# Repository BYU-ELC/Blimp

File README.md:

# Air Blimp
Sources, code, and files for the Air Blimp project

This code is implemented as a Bluetooth app. 
A helium balloon will keep the blimp suspended in air. This Bluetooth app will have access to the vector thrusters on either side, and when signified, these will steer the blimp in the desired direction.

This main  folder includes:
<br>The PCB Schematic File:     Blimp PCB v27.sch
<br>The PCB Board File:         Blimp_PCB_v50.brd
<br>The Laser cut vector file:  blimp_cut_v3.dxf
<br>The Arduino Code:           blimp.ino

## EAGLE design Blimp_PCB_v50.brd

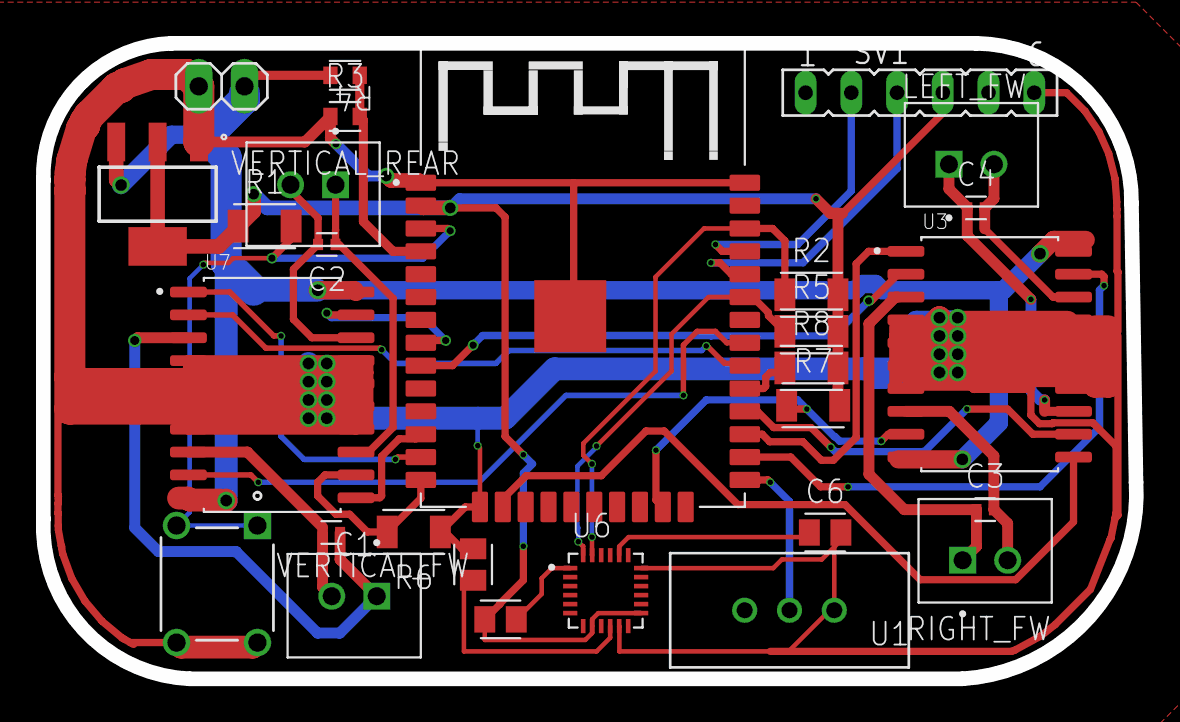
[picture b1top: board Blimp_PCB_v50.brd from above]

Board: 2 copper layers, 60.7 x 35.3 mm, 28 parts (0 on the bottom side), 34 nets.

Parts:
BATTERY_CONN: PINHD-1X2; 1X02
C1, C2, C3, C4: 330p; CAPC1005X60
C5: .1uF; CAPC2012X110
C6: 2200pF; CAPC2012X110
C7: .01uF; CAPC2012X110
LEFT_FW: B2B-XH-A(LF)(SN); JST_B2B-XH-A(LF)(SN)
R1, R6, R7, R8: RESC3216X70
R2, R5: 4.7k; RESC3216X70
R3, R4: RESC1608X60
RESETBUTTON: 1-1825910-0; SWITCH_1-1825910-0
RIGHT_FW: B2B-XH-A(LF)(SN); JST_B2B-XH-A(LF)(SN)
SV1: FE06
U1: 1825159-1; SW3-SLIDE-2POL_P98
U3, U7: L293DD; SOIC127P1032X265-20N
U4: LD1117S33TR; SOT230P700X180-4N
U5: ESP-WROOM-32; MODULE_ESP-WROOM-32
U6: MPU-6050; QFN50P400X400X95-24N
VERTICAL_FW: B2B-XH-A(LF)(SN); JST_B2B-XH-A(LF)(SN)
VERTICAL_REAR: B2B-XH-A(LF)(SN); JST_B2B-XH-A(LF)(SN)

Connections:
GND: BATTERY_CONN.2, C5.1, C6.2, R3.1, R6.1, RESETBUTTON.3, RESETBUTTON.4, SV1.6, U1.3, U3.4, U3.5, U3.6, U3.7, U3.14, U3.15, U3.16, U3.17, U4.1, U5.1, U5.1.1, U5.15, U5.38, U6.11, U6.18, U7.4, U7.5, U7.6, U7.7, U7.14, U7.15, U7.16, U7.17
IO0: U1.2, U5.25
IO4: U3.19, U5.26
IO5: R8.1, U5.29
IO12: R6.2, U5.14, U7.12
IO13: U3.11, U5.16
IO14: U5.13, U7.1
IO15: R7.1, U3.9, U5.23
IO16: U3.1, U5.27
IO17: U3.12, U5.28
IO18: U5.30, U7.2
IO19: U5.31, U7.9
IO21: R5.1, U5.33, U6.24
IO22: R2.1, U5.36, U6.23
IO27: U5.12, U7.11
IO32: U5.8, U7.19
IO33: U3.2, U5.9
IO36: R3.2, R4.1, U5.4
unnamed: C3.1, RIGHT_FW.1, U3.3
unnamed: C3.2, RIGHT_FW.2, U3.8
unnamed: C4.1, LEFT_FW.1, U3.13
unnamed: C1.1, U7.8, VERTICAL_FW.2
unnamed: C1.2, U7.3, VERTICAL_FW.1
unnamed: C2.1, U7.13, VERTICAL_REAR.1
unnamed: C2.2, U7.18, VERTICAL_REAR.2
unnamed: SV1.2, U5.35
unnamed: C6.1, U6.20
unnamed: C5.2, U6.10
unnamed: C7.2, U6.1
unnamed: C4.2, LEFT_FW.2, U3.18
unnamed: SV1.3, U5.34
RESET: R1.2, RESETBUTTON.1, RESETBUTTON.2, U5.3
VBATT: BATTERY_CONN.1, R4.2, U3.10, U3.20, U4.3, U7.10, U7.20
VCC: C7.1, R1.1, R2.2, R5.2, R7.2, R8.2, SV1.4, U4.2, U4.4, U5.2, U6.8, U6.13

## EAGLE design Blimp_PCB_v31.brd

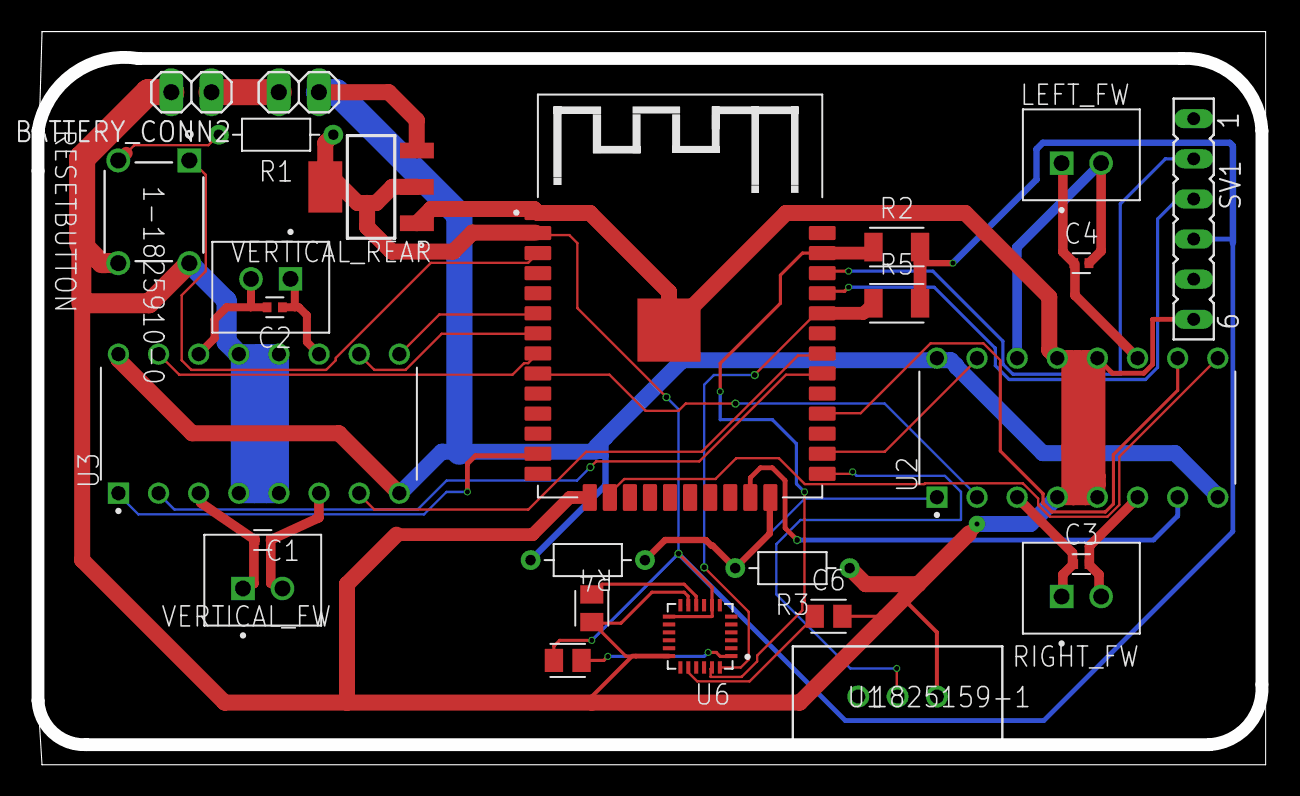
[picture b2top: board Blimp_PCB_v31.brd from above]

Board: 2 copper layers, 77.5 x 45.6 mm, 26 parts (0 on the bottom side), 34 nets.

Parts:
BATTERY_CONN, BATTERY_CONN2: PINHD-1X2; 1X02
C1, C2, C3, C4: 330p; CAPC1005X60
C5: .1uF; CAPC2012X110
C6: 2200pF; CAPC2012X110
C7: .01uF; CAPC2012X110
LEFT_FW: B2B-XH-A(LF)(SN); JST_B2B-XH-A(LF)(SN)
R1: 10k; RESAD724W46L381D178B
R2, R5: 4.7k; RESC3216X70
R3, R4: RESAD724W46L381D178B
RESETBUTTON: 1-1825910-0; SWITCH_1-1825910-0
RIGHT_FW: B2B-XH-A(LF)(SN); JST_B2B-XH-A(LF)(SN)
SV1: FE06
U1: 1825159-1; SW3-SLIDE-2POL_P98
U2, U3: L293D; DIP880W50P254L2000H510Q16
U4: LD1117S33TR; SOT230P700X180-4N
U5: ESP-WROOM-32; MODULE_ESP-WROOM-32
U6: MPU-6050; QFN50P400X400X95-24N
VERTICAL_FW: B2B-XH-A(LF)(SN); JST_B2B-XH-A(LF)(SN)
VERTICAL_REAR: B2B-XH-A(LF)(SN); JST_B2B-XH-A(LF)(SN)

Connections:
GND: BATTERY_CONN2.2, C5.1, C6.2, R3.1, RESETBUTTON.3, RESETBUTTON.4, SV1.6, U1.3, U2.4, U2.5, U2.12, U2.13, U3.4, U3.5, U3.12, U3.13, U4.1, U5.1, U5.1.1, U5.15, U5.38, U6.11, U6.18
IO0: U1.2, U5.25
IO2: R3.2, R4.1, U2.1, U5.24
IO4: U2.15, U5.26
IO13: U2.9, U5.16
IO14: U3.1, U5.13
IO15: U2.7, U5.23
IO17: U2.10, U5.28
IO18: U3.2, U5.30
IO19: U3.7, U5.31
IO21: R5.1, U5.33, U6.24
IO22: R2.1, U5.36, U6.23
IO32: U3.15, U5.8
IO33: U2.2, U5.9
IO34: U3.9, U5.6
IO35: U3.10, U5.7
unnamed: C3.1, RIGHT_FW.1, U2.3
unnamed: C3.2, RIGHT_FW.2, U2.6
unnamed: C4.1, LEFT_FW.1, U2.11
unnamed: C4.2, LEFT_FW.2, U2.14
unnamed: C1.1, U3.3, VERTICAL_FW.1
unnamed: C1.2, U3.6, VERTICAL_FW.2
unnamed: C2.1, U3.11, VERTICAL_REAR.1
unnamed: C2.2, U3.14, VERTICAL_REAR.2
unnamed: SV1.2, U5.35
unnamed: C6.1, U6.20
unnamed: C5.2, U6.10
unnamed: BATTERY_CONN.2, BATTERY_CONN2.1
unnamed: C7.2, U6.1
unnamed: R1.2, RESETBUTTON.2
unnamed: SV1.3, U5.34
RESET: RESETBUTTON.1, U5.3
VBATT: BATTERY_CONN.1, R4.2, U2.8, U2.16, U3.8, U3.16, U4.3
VCC: C7.1, R1.1, R2.2, R5.2, SV1.4, U4.2, U4.4, U5.2, U6.8, U6.13

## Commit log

2021-05-28 Update blimp.ino
    Added remote code functionality, made connection to the blimp require a password, and eliminated the potential for multiple connected controllers.
2021-06-01 added vertical motor control
2021-06-02 Update blimp.ino
    Added imu sensor reading
2021-06-02 fixing broken code
2021-06-02 reverting code
2021-06-02 Update blimp.ino
    Readded Accelerometer code
2021-06-02 updated gpio pin number
2021-06-09 Update blimp.ino
    Fixed the app so that the password you type in doesn't disappear quickly.
2021-07-17 Updated IO Pins
2021-08-16 Updated changes to include sending of battery voltage to the app
2021-10-05 Delete Blimp_PCB_v31.brd
    This is outdated
2021-10-05 Delete Blimp_PCB_v19.sch
    outdated
2021-10-05 Add files via upload
    These are the final versions as of the end of summer 2021.

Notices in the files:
parts and their libraries:
COPYRIGHT: Copyright (C) 2016 Accelerated Designs. All rights reserved
